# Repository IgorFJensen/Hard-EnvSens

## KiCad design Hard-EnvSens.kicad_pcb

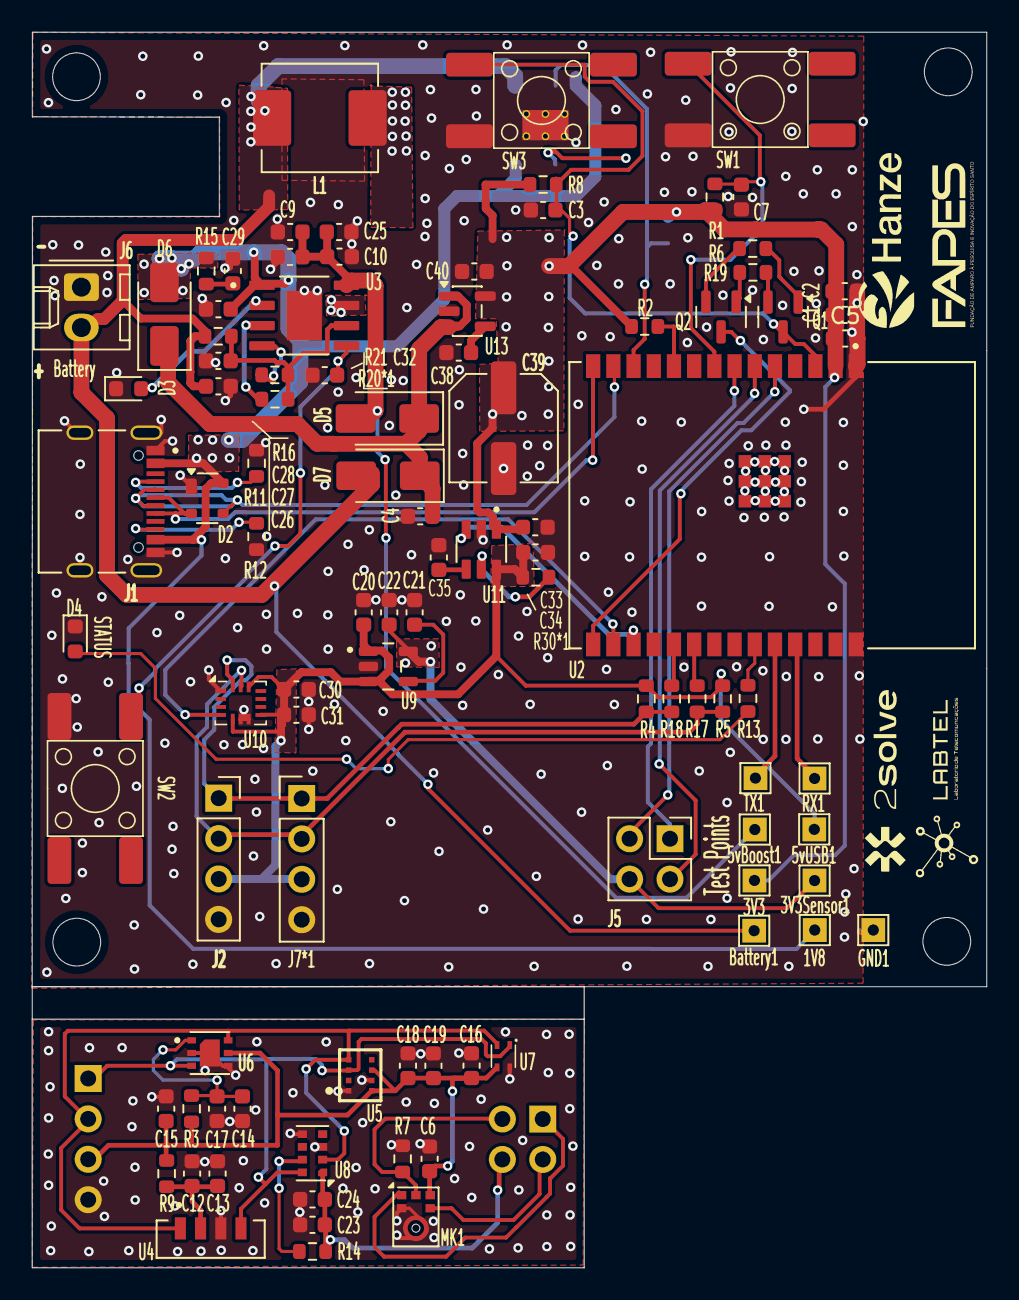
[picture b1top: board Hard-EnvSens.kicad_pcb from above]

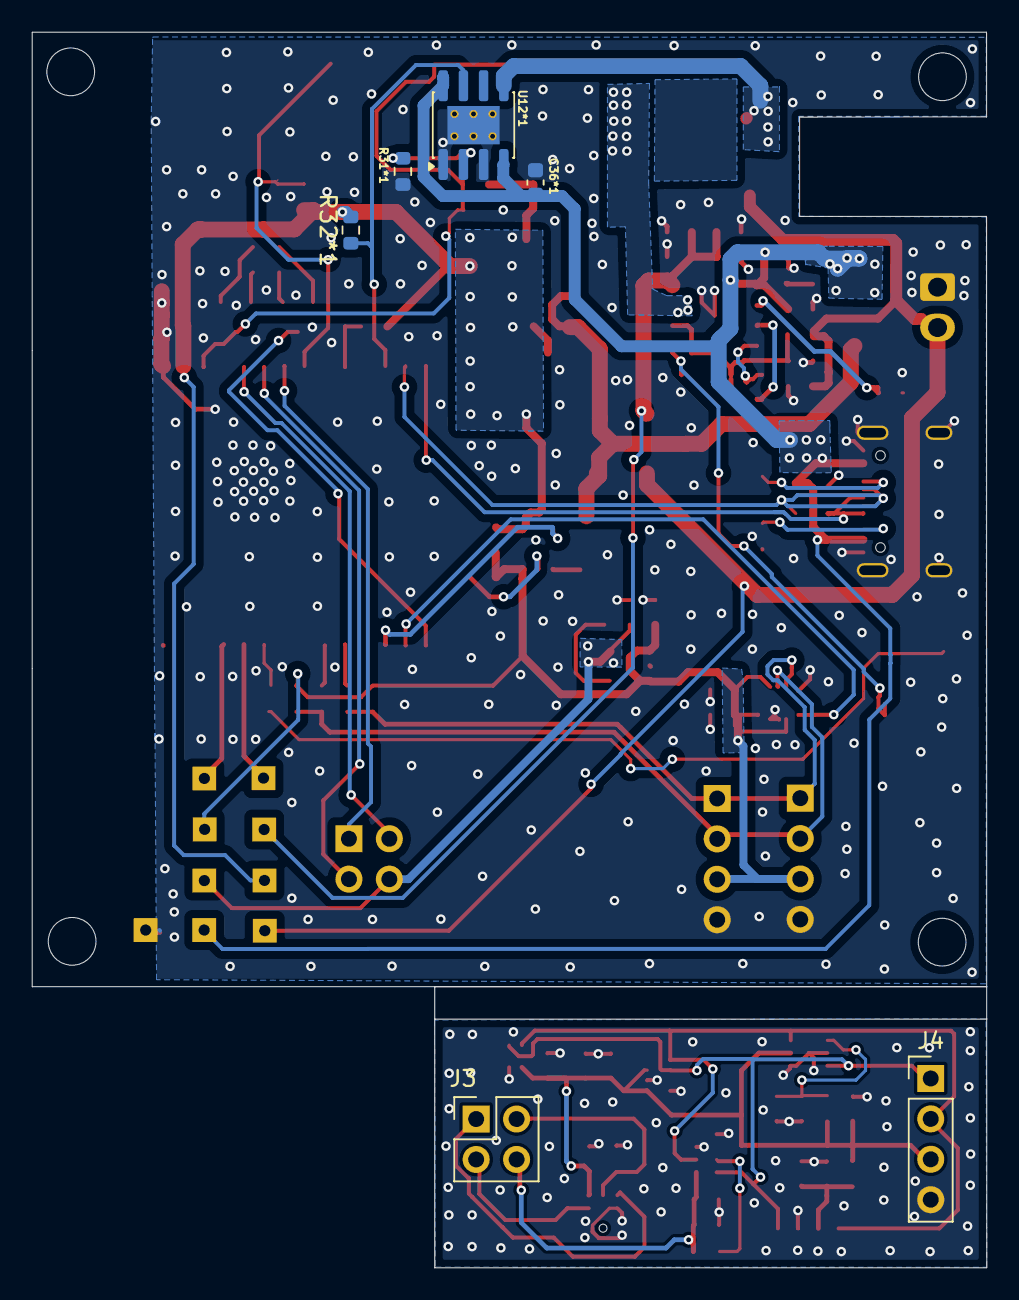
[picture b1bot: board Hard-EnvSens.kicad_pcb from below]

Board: 2 copper layers, 60.0 x 77.7 mm, 102 parts (6 on the bottom side), 57 nets.

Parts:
1V8, 3V3, 3V3Sensor1, 5vBoost1, 5vUSB1: TestPoint; TestPoint_THTPad_1.5x1.5mm_Drill0.7mm
Battery1: TestPoint; TestPoint_THTPad_1.5x1.5mm_Drill0.7mm
C1, C4, C5, C13, C22, C28, C29, C36*1: 10uF; C_0603_1608Metric
C2, C12, C16, C18, C19, C23, C30, C31, C32: 100nF; C_0603_1608Metric
C3, C7, C14, C15, C33: 1uF; C_0603_1608Metric
C6, C24: 4.7uF; C_0603_1608Metric
C8, C9, C10, C25, C26, C27: 22uF; C_0603_1608Metric
C17, C38: 10nF; C_0603_1608Metric
C20, C34, C40: 0.1uF; C_0603_1608Metric
C21: 0.01uF; C_0603_1608Metric
C35: 1nF; C_0603_1608Metric
C39: 100uF; C_Elec_6.3x7.7
D2: SP0503BAHT; SOT-143
D3, D4: LED; LED_0603_1608Metric
D5, D6, D7: CMS30I30A; D_SMA
GND1: TestPoint; TestPoint_THTPad_1.5x1.5mm_Drill0.7mm
J1: TYPE-C-31-M-12; HRO_TYPE-C-31-M-12
J2: Conn_01x04_Socket; PinSocket_1x04_P2.54mm_Vertical
J3: Conn_02x02_Odd_Even; PinHeader_2x02_P2.54mm_Vertical
J4, J7*1: Conn_01x04_Pin; PinHeader_1x04_P2.54mm_Vertical
J5: Conn_02x02_Odd_Even; PinSocket_2x02_P2.54mm_Vertical
J6: Conn_01x02_Pin; Molex_KK-254_AE-6410-02A_1x02_P2.54mm_Vertical
L1: 1uH; L_TechFuse_SL0630
MK1: ICS-43434; InvenSense_ICS-43434-6_3.5x2.65mm
Q1, Q2: SS8050; SOT-23
R1, R2, R8, R14, R32*1: 10k; R_0603_1608Metric
R3: 4.7R; R_0603_1608Metric
R4, R5: 4.7k; R_0603_1608Metric
R6, R19: 12k; R_0603_1608Metric
R7: 100K; R_0603_1608Metric
R9: 10R; R_0603_1608Metric
R11, R12: 5.11k; R_0603_1608Metric
R13, R21: 1k; R_0603_1608Metric
R15: 2R; R_0603_1608Metric
R16: 0.5R; R_0603_1608Metric
R17, R18, R30*1: 0R; R_0603_1608Metric
R20*1: 100k; R_0603_1608Metric
R31*1: 4k; R_0603_1608Metric
RX1: TestPoint; TestPoint_THTPad_1.5x1.5mm_Drill0.7mm
SW1, SW2, SW3: SW_Push; Botao KH-6X6X5H-STM
TX1: TestPoint; TestPoint_THTPad_1.5x1.5mm_Drill0.7mm
U2: ESP32-C6-WROOM-1; XCVR_ESP32-C6-WROOM-1-N8
U3: IP5306; SOP127P600X165-9N
U4: VEML7700-TR; XDCR_VEML7700-TR
U5: DPS368; LGA8S145X65P2X4_200X250X110-V
U6: SGP41-D-R4; XDCR_SGP41-D-R4
U7: SHT40-AD1B-R2; SHT4X
U8: AS7341-DLGT; AMS_OLGA-8_2x3.1mm_P0.8mm
U9: TPS79318DBVTG4; SOT95P280X145-5N
U10: BMI160; Bosch_LGA-14_3x2.5mm_P0.5mm
U11: TPS22918TDBVRQ1; SOT95P280X145-6N
U12*1: TP4056-42-ESOP8; SOIC-8-1EP_3.9x4.9mm_P1.27mm_EP2.41x3.3mm_ThermalVias
U13: SPX3819M5-L-3-3; SOT-23-5

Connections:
3v3_aux: 3V3Sensor1.1, C20.1, C30.1, C31.1, C34.1, J2.3, J7*1.3, R4.2, R5.2, R30*1.1, U9.1 (IN), U9.3 (EN), U10.5 (VDDIO), U10.8 (VDD), U10.12 (CSB), U11.6 (VOUT)
+1V8: 1V8.1, C22.1, J5.4, U9.5 (OUT)
+1V8top: C23.1, C24.1, J3.4, R14.2, U8.1 (VDD)
+3V3: 3V3.1, C1.1, C2.1, C5.1, C33.1, C39.1, C40.1, R1.1, R2.1, R8.1, R32*1.2, U2.2 (3V3), U11.1 (VIN), U13.5 (OUT)
+3V3top: C6.1, C15.1, C16.1, C18.1, C19.1, J4.3, MK1.5 (VDD), R3.2, R9.2, U5.6 (VDDIO), U5.8 (VDD), U6.5 (VDDH), U7.3 (VDD)
+5V: 5vUSB1.1, C28.1, C36*1.1, D2.4 (K), D6.2 (A), J1.A4_B9 (VBUS), J1.B4_A9 (VBUS), R15.1, U3.1 (VIN), U12*1.4 (V_{CC}), U12*1.8 (CE)
+5vBat: 5vBoost1.1, C8.1, C9.1, C10.1, C25.1, D5.2 (A), U3.8 (VOUT)
Bat+: Battery1.1, C27.1, D7.2 (A), J6.2, L1.2, R16.1, U12*1.5 (BAT)
Charge_Bat: R32*1.1, U2.12 (GPIO11), U12*1.7 (~CHRG)
D+: D2.2 (K), J1.A6 (DP1), J1.B6 (DP2), U2.14 (GPIO13/USB_D+)
D-: D2.3 (K), J1.A7 (DN1), J1.B7 (DN2), U2.13 (GPIO12/USB_D-)
DTR: Q2.2 (E), R6.2
EN: C3.1, Q1.3 (C), R8.2, SW3.2, U2.3 (EN/CHIP_PU)
GND: C1.2, C2.2, C3.2, C4.2, C5.2, C7.2, C8.2, C9.2, C10.2, C20.2, C21.2, C22.2, C25.2, C26.2, C27.2, C28.2, C29.2, C30.2, C31.2, C32.2, C33.2, C34.2, C35.2, C36*1.2, C38.2, C39.2, C40.2, D2.1 (A), D3.1 (K), D4.1 (K), GND1.1, J1.A1_B12 (GND), J1.B1_A12 (GND), J1.S1 (SHIELD), J1.S2 (SHIELD), J1.S3 (SHIELD), J1.S4 (SHIELD), J2.4, J6.1, J7*1.4, R11.2, R12.2, R31*1.2, SW1.1, SW2.1, SW3.1, U2.1 (GND), U2.28 (GND), U3.9 (POWERPAD), U9.2 (GND), U10.1 (SDO), U10.6 (GNDIO), U10.7 (GND), U11.2 (GND), U12*1.1 (TEMP), U12*1.3 (GND), U12*1.9 (EPAD), U13.2 (GND)
GND2: C6.2, C12.2, C13.2, C14.2, C15.2, C16.2, C17.2, C18.2, C19.2, C23.2, C24.2, J4.4, MK1.2 (LR), MK1.3 (GND), R7.1, U4.3 (GND), U5.1 (GND_1), U5.7 (GND_2), U6.2 (VSS), U6.4 (N/A), U6.7 (EXP), U7.4 (VSS), U8.3 (GND), U8.5 (PGND)
IO9: Q2.3 (C), U2.15 (GPIO9)
Int1: U2.16 (GPIO18), U10.4 (INT1)
unnamed: C29.1, R15.2
unnamed: D3.2 (A), U3.2 (LED1)
unnamed: D4.2 (A), R13.1
unnamed: C4.1, D5.1 (K), D6.1 (K), D7.1 (K), U13.1 (IN), U13.3 (EN)
unnamed: J1.A5 (CC1), R11.1
unnamed: J1.B5 (CC2), R12.1
unnamed: Q1.1 (B), R6.1
unnamed: Q2.1 (B), R19.2
unnamed: C7.1, R1.2, SW1.2, U2.8 (GPIO0/ADC1_CH0/XTAL_32K_P)
unnamed: R2.2, U2.10 (GPIO8)
unnamed: R13.2, U2.23 (GPIO15)
unnamed: R18.1, U2.19 (GPIO21)
unnamed: R17.1, U2.20 (GPIO22)
unnamed: C26.1, R16.2, R20*1.2, R21.2, U3.6 (BAT)
unnamed: C32.1, SW2.2, U3.5 (KEY)
unnamed: R20*1.1, U3.3 (LED2)
unnamed: R21.1, U3.4 (LED3)
unnamed: L1.1, U3.7 (SW)
unnamed: C12.1, C13.1, R9.1, U4.2 (VDD)
unnamed: C14.1, C17.1, R3.1, U6.1 (VDD)
unnamed: R14.1, U8.7 (INT)
unnamed: C21.1, U9.4 (NR)
unnamed: C35.1, U11.4 (CT)
unnamed: R30*1.2, U11.5 (QOD)
unnamed: R31*1.1, U12*1.2 (PROG)
unnamed: C38.1, U13.4 (BP)
RTS: Q1.2 (E), R19.1
RX: RX1.1, U2.25 (U0TXD/GPIO16)
SCK: J5.3, U2.6 (MTCK/GPIO6/ADC1_CH6)
SCKtop: J3.3, MK1.4 (SCK)
SD: J5.2, U2.5 (MTDI/GPIO5/ADC1_CH5)
SDtop: J3.2, MK1.6 (SD), R7.2
Scl: J2.2, J7*1.2, R5.1, R17.2, U10.13 (SCx)
Scltop: J4.2, U4.1 (SCL), U5.4 (SCK), U6.6 (SCL), U7.2 (SCL), U8.2 (SCL)
Sda: J2.1, J7*1.1, R4.1, R18.2, U10.14 (SDx)
Sdatop: J4.1, U4.4 (SDA), U5.3 (SDI), U6.3 (SDA), U7.1 (SDA), U8.8 (SDA)
Sensors_3v3: U2.17 (GPIO19), U11.3 (ON)
TX: TX1.1, U2.24 (U0RXD/GPIO17)
WS: J5.1, U2.7 (MTDO/GPIO7)
WStop: J3.1, MK1.1 (WS)

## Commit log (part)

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2025-11-20 Correct files names
2025-11-28 Added some sensors
2025-12-05 Some corrections
    Reviewed
2025-12-05 Dps368
2025-12-12 as7341 added
2026-01-07 Libraries
2026-01-08 New sensors
2026-01-20 Sch done
2026-01-20 footprint
2026-01-22 Schematic done, Bottom board
2026-01-29 Started connections and sensors pcb
2026-02-04 Full connected board, no charger
2026-02-06 Battery charger (not reviewed)
2026-02-12 Baterry charger + giroscope
    Magnetometer not connected
2026-02-12 Correct commit for battery charger
2026-02-25 Save commit
2026-02-26 Improved whole board design
2026-02-26 Lot of improvements
2026-03-04 Logos and corrections
2026-03-26 New charger + 3v3 Switch
2026-03-26 small changes + gotta fix the charger
    Maybe rotating the charger 2 gets a better pin configuration
2026-03-26 Almost finished board
    New 3v3 regulaator
2026-03-27 Almost ready to fabricate
2026-03-27 ready to fabricate
